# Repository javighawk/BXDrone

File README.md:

BXDrone
=======
BXDrone is a project that aims to develop a flight controller using an Arduino or Arduino-compatible  board, which would be aboard a quadcopter and will be receiving telecommands and sending telemetry to and from a computer. The Arduino board will use an IMU (Inertial Measurement Unit) to determine the pitch, roll and yaw angles and keep them on a desired value. The communication is intented to be wireless through XBee modules. However, for testing, a wired-serial communication through USB can be done.

While most of the projects suggest to buy a flight controller and build a drone with it, the objective of this project is to get a deep insight on how the flight controller works, which problems can generate and how to solve them.

Please refer to doc/ folder for further documentation.

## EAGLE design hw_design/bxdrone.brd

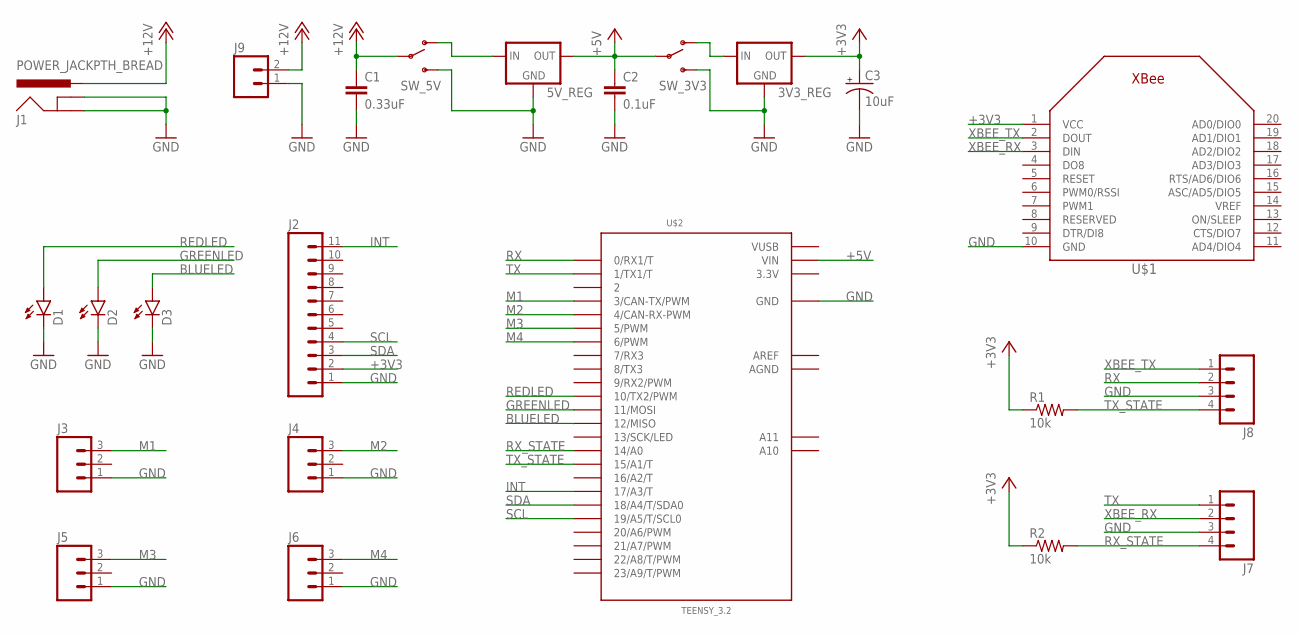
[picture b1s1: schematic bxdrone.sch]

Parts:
3V3_REG: LD1117V33; TO-220-STANDING
5V_REG: L78S05CV; TO-220-STANDING
C1: 0.33uF; CAP-PTH-SMALL
C2: 0.1uF; CAP-PTH-SMALL
C3: 10uF; CPOL-RADIAL-10UF-25V
D1, D2, D3: LED5MM
J1: POWER_JACKPTH_BREAD; POWER_JACK_PTH_BREAD
J2: M11PTH; 1X11
J3, J4, J5, J6: M03PTH; 1X03
J7, J8: M04PTH; 1X04
J9: M02JST-PTH-VERT; JST-2-PTH-VERT
R1, R2: 10k; AXIAL-0.4
SW_3V3, SW_5V: SWITCH-SPDTPTH; SWITCH-SPDT
U$1: XBEE
U$2: TEENSY_3.2; TEENSY3-DIL+4

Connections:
3.3V: U$2.3.3V
+3V3: 3V3_REG.2 (OUT), C3.1 (+), J2.2, R1.P$1 (1), R2.P$1 (1), U$1.1 (VCC)
+5V: 5V_REG.3 (OUT), C2.1, SW_3V3.2, U$2.VIN
+12V: C1.1, J1.PWR, J9.2, SW_5V.2
AGND: U$2.AGND
AREF: U$2.AREF
BLUELED: D3.A, U$2.12 (12/MISO)
GND: 3V3_REG.1 (GND), 5V_REG.2 (GND), C1.2, C2.2, C3.2 (-), D1.K (C), D2.K (C), D3.K (C), J1.GND, J1.GNDBREAK, J2.1, J3.1, J4.1, J5.1, J6.1, J7.3, J8.3, J9.1, SW_3V3.3 (S), SW_5V.3 (S), U$1.10 (GND), U$2.GND
GREENLED: D2.A, U$2.11 (11/MOSI)
INT: J2.11, U$2.17/A3 (17/A3/T)
M1: J3.3, U$2.3 (3/CAN-TX/PWM)
M2: J4.3, U$2.4 (4/CAN-RX-PWM)
M3: J5.3, U$2.5 (5/PWM)
M4: J6.3, U$2.6 (6/PWM)
unnamed: 5V_REG.1 (IN), SW_5V.1 (O)
unnamed: 3V3_REG.3 (IN), SW_3V3.1 (O)
REDLED: D1.A, U$2.10 (10/TX2/PWM)
RX: J8.2, U$2.0 (0/RX1/T)
RX_STATE: J7.4, R2.P$2 (2), U$2.14/A0
SCL: J2.4, U$2.19/A5 (19/A5/T/SCL0)
SDA: J2.3, U$2.18/A4 (18/A4/T/SDA0)
TX: J7.1, U$2.1 (1/TX1/T)
TX_STATE: J8.4, R1.P$2 (2), U$2.15/A1 (15/A1/T)
VUSB: U$2.VUSB
XBEE_RX: J7.2, U$1.3 (DIN)
XBEE_TX: J8.1, U$1.2 (DOUT)

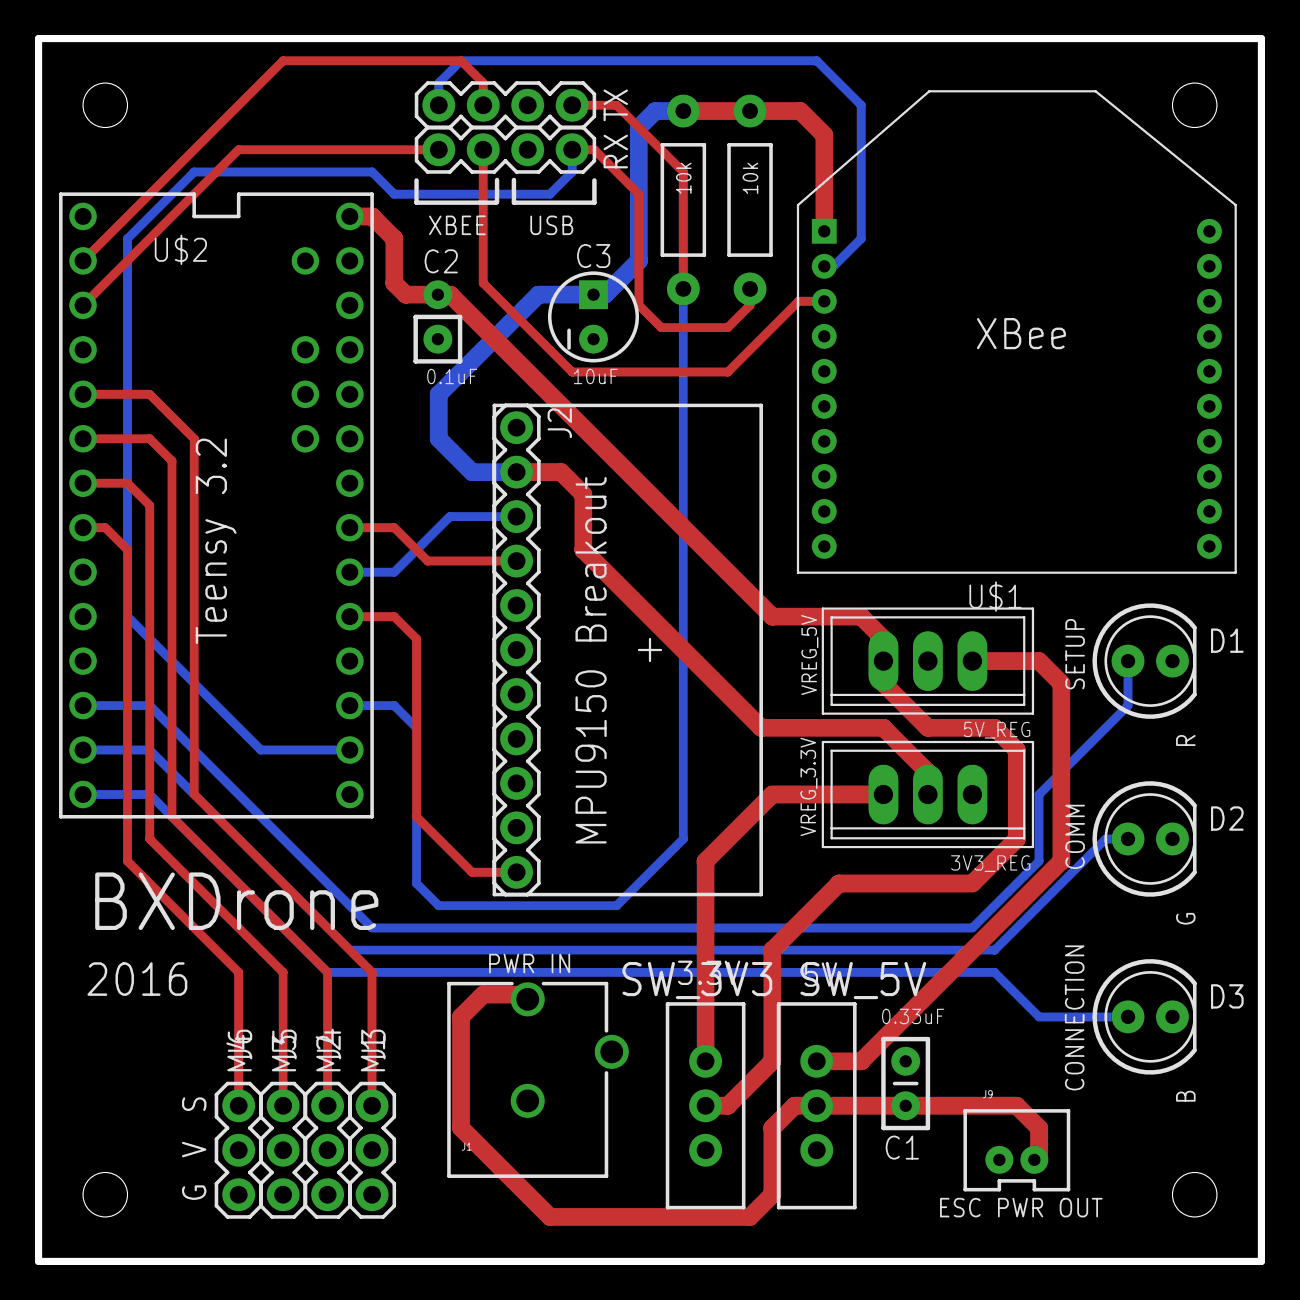
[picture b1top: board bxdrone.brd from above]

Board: 2 copper layers, 69.8 x 69.8 mm, 23 parts (0 on the bottom side), 22 nets.

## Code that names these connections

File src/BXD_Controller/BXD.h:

#ifndef BXD_h
#define BXD_h

/*********************************************************/
/********************* INCLUDES **************************/
/*********************************************************/

#include "Arduino.h"


/*********************************************************/
/******************** MODES DEFINES **********************/
/*********************************************************/

#define MODE_MASK               0x0F
#define MOVE_Z_MODE             0x00
#define MOVE_PR_MODE            0x01
#define MOVE_YAW_MODE           0x02
#define COMMAND_MODE            0x04


/*********************************************************/
/****************** COMM PACKAGE DEFINES *****************/
/*********************************************************/

#define ENDOFTM                 0x05
#define TELEMETRY               0x0E
#define TM_PETITION             0x0F
#define ENDOFPCK                0x88
#define ESC                     0x7E
#define TM_CONFIRMATION         0x80


/*********************************************************/
/********************* PIN DEFINES ***********************/
/*********************************************************/

#define MOTOR1_PIN                3
#define MOTOR2_PIN                4
#define MOTOR3_PIN                5
#define MOTOR4_PIN                6
#define SETUPLED_PIN              10
#define COMMLED_PIN               11
#define CONNECTIONLED_PIN         12
#define IMU_INTERRUPTPIN          17



/*********************************************************/
/********************* LED DEFINES ***********************/
/*********************************************************/

#define REDLED_PIN                SETUPLED_PIN
#define GREENLED_PIN              COMMLED_PIN
#define BLUELED_PIN               CONNECTIONLED_PIN


/*********************************************************/
/******************** OTHER DEFINES **********************/
/*********************************************************/

#define SERIAL_BPS          115200
#define ON                        1
#define OFF                       0


#endif

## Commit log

2014-12-31 07-28-2014 Version
    Latest version of BXD on this date
2015-01-29 Moved folder
    Arduino programs needs to be inside a folder with the same name as the
    ".ino" file.
2015-01-30 IMU Managing files
    I have created the files that contain the functions in order to get the
    readings from the IMU, perform any modifications on the device and
    compute the angles.
2015-01-31 IMU fuctions added
    This is the first compiling version for Arduino in which the functions
    of the IMU are added. At the moment only the accelerometer and gyro
    reaedings are used, so the other functionalities are still not
    implemented, so this is still under construction. At this moment it
    compiles but it hasn't been tested on the board yet.
    Issues for Intel Galileo board:
2015-03-19 IMU functions finished
    All the code has been adapted to the new IMU
2015-06-06 RXTXSerial Library update
    Updated the RXTXSerial library download link to include both 64-bit and 32-bit versions
2015-06-10 Monitoring processing time
    - Modified the Move mode code in Arduino. The space bar now sends a
    Short Command (instead of a Move mode byte) to stop all the motors.
    - Added the calculation of the time (last, maximum and average) between
    two calls to the function IMU.getMotion6 to know the average sampling
    time for accelerometer and gyroscope data. Aimed to be less than 1ms,
    which is the sampling time for the Accelerometer in the IMU. Also added
2015-06-13 Minor changes
    Minor changes on the function names on the BXCommandMode.cpp file and on
    the "delta" times calculation on IMUManager.cpp file
2015-06-13 Fixed minor details on GUI
    Some buttons were activated when the Serial port was not connected yet,
    or they remained deactivated when the port was already open. Fixed now.
2015-06-15 Angles calculation & PID modifications
    - Angles are calculated on Arduino using only accelerometer data.
    - We have now 2 PIDs controlling the angles (pitch and roll) and other
    two reacting against gyroscope (from X and Y axis) readings. The
    gyroscope readings will be used to stabilize the quadcopter while the
    other two PIDs will try to achieve a desired angle.
    - Now the parameter "maxdelta" will record the maximum delta value from
2015-06-18 Fastest version of the program
    -Fastest code achieved. It still has around 1.2 ms of average time
    between accel/gyro sample requests, that means that we would be losing 1
    out of 6 samples. We will see if this is fast enough or whether we need
    to improve it.
2015-06-19 Calculating angles on the Computer side
    Removed pitch and roll angles telemetry since they are not being
    calculated on the drone, but on the computer. The drone receives the
    desired pitch and roll angles and calculates the accelerometer values
    needed in order to get the desired pitch and roll values.
2015-07-01 Folder name changed
2015-07-09 Added "set maximum speed" function
    Added the possibility of setting all motors to maximum speed by hitting
    the back space. This is implemented for ESC calibration purposes only.
2015-08-22 Added README.md
2015-08-22 Modified README.md
2015-08-22 Added time telemetry to GUI
    Added progress bars to display the delta times. Added running time
    telemetry
2015-08-24 Added Data Recording feature
    Added the Data Recording feature from the Java computer application. A
    Matlab script has been designed in order to take the data generated by
    the Java application and plot it.
2015-08-29 Added precision on PID values
    The precision on the PID values has been aumented to 4 decimals
2015-09-29 Added libraries
    Added libraries to the Arduino folder. To use them, Go to Sketch ->
    Import library -> Add library and select all the libraries included
    here.
    Removed unused functions on the Arduino program
2016-07-22 Brand new code. Version 0.1
2016-07-22 Reorganized folders
2016-07-22 Added doc example
2016-07-22 Added doc content
2016-07-22 Removed unused library
2016-07-22 Changed Java project name
2016-07-22 Added software to doc
2016-07-22 Added Matlab code for plotting recorded data
2016-07-22 Updated doc
2016-07-22 Added Matlab on doc's software section
2016-07-25 Added comments
2016-07-25 Adapted PID output limits
2016-07-25 Changed PID Kv's scaling and Gyro values display limits
2016-07-25 Binaries
2016-07-25 Added time records for main loop and IMU interruption
2016-07-25 Added TimeRecord class
2016-07-25 Added telemetry for TimeRecord objects
2016-07-30 Modified one of the tracks on the bottom side
2016-07-31 Added TimeRecord object to measure telemetry time
2016-07-31 Added doc
2016-07-31 Revert "Time record"
2016-07-31 Starting to change board design
2016-07-31 Finished board rearrangement
2016-08-02 Changed connection with XBee and holes positions in board
2016-08-02 Modifications on schematic
2016-08-02 Unable speed controller COM box when connected
2016-08-06 Added bottom labels and signature
2016-08-06 Fixed DRC errors
2016-08-06 Added Gerber files
2016-08-06 Removed measurements
2016-08-06 Changed font on silkscreen. Regenerated Gerbers

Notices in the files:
parts and their libraries:
SparkFun-Capacitors: Licensing: Creative Commons ShareAlike 4.0 International - https://creativecommons.org/licenses/by-sa/4.0
